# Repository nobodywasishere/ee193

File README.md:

# ee193

## Useful links

- https://www.seeedstudio.com/LoRa-E5-Dev-Kit-p-4868.html
- https://www.st.com/en/microcontrollers-microprocessors/stm32wle5jc.html#
- https://www.digikey.com/en/products/detail/seeed-technology-co-ltd/113990934/13926230

- https://docs.platformio.org/en/latest/boards/ststm32/nucleo_wl55jc.html
- https://github.com/platformio/platform-ststm32/blob/develop/boards/nucleo_wl55jc.json
- https://docs.zephyrproject.org/2.7.0/boards/arm/lora_e5_dev_board/doc/lora_e5_dev_board.html
- https://doc.riot-os.org/group__boards__lora-e5-dev.html

- https://www.st.com/en/development-tools/stm32cubeprog.html

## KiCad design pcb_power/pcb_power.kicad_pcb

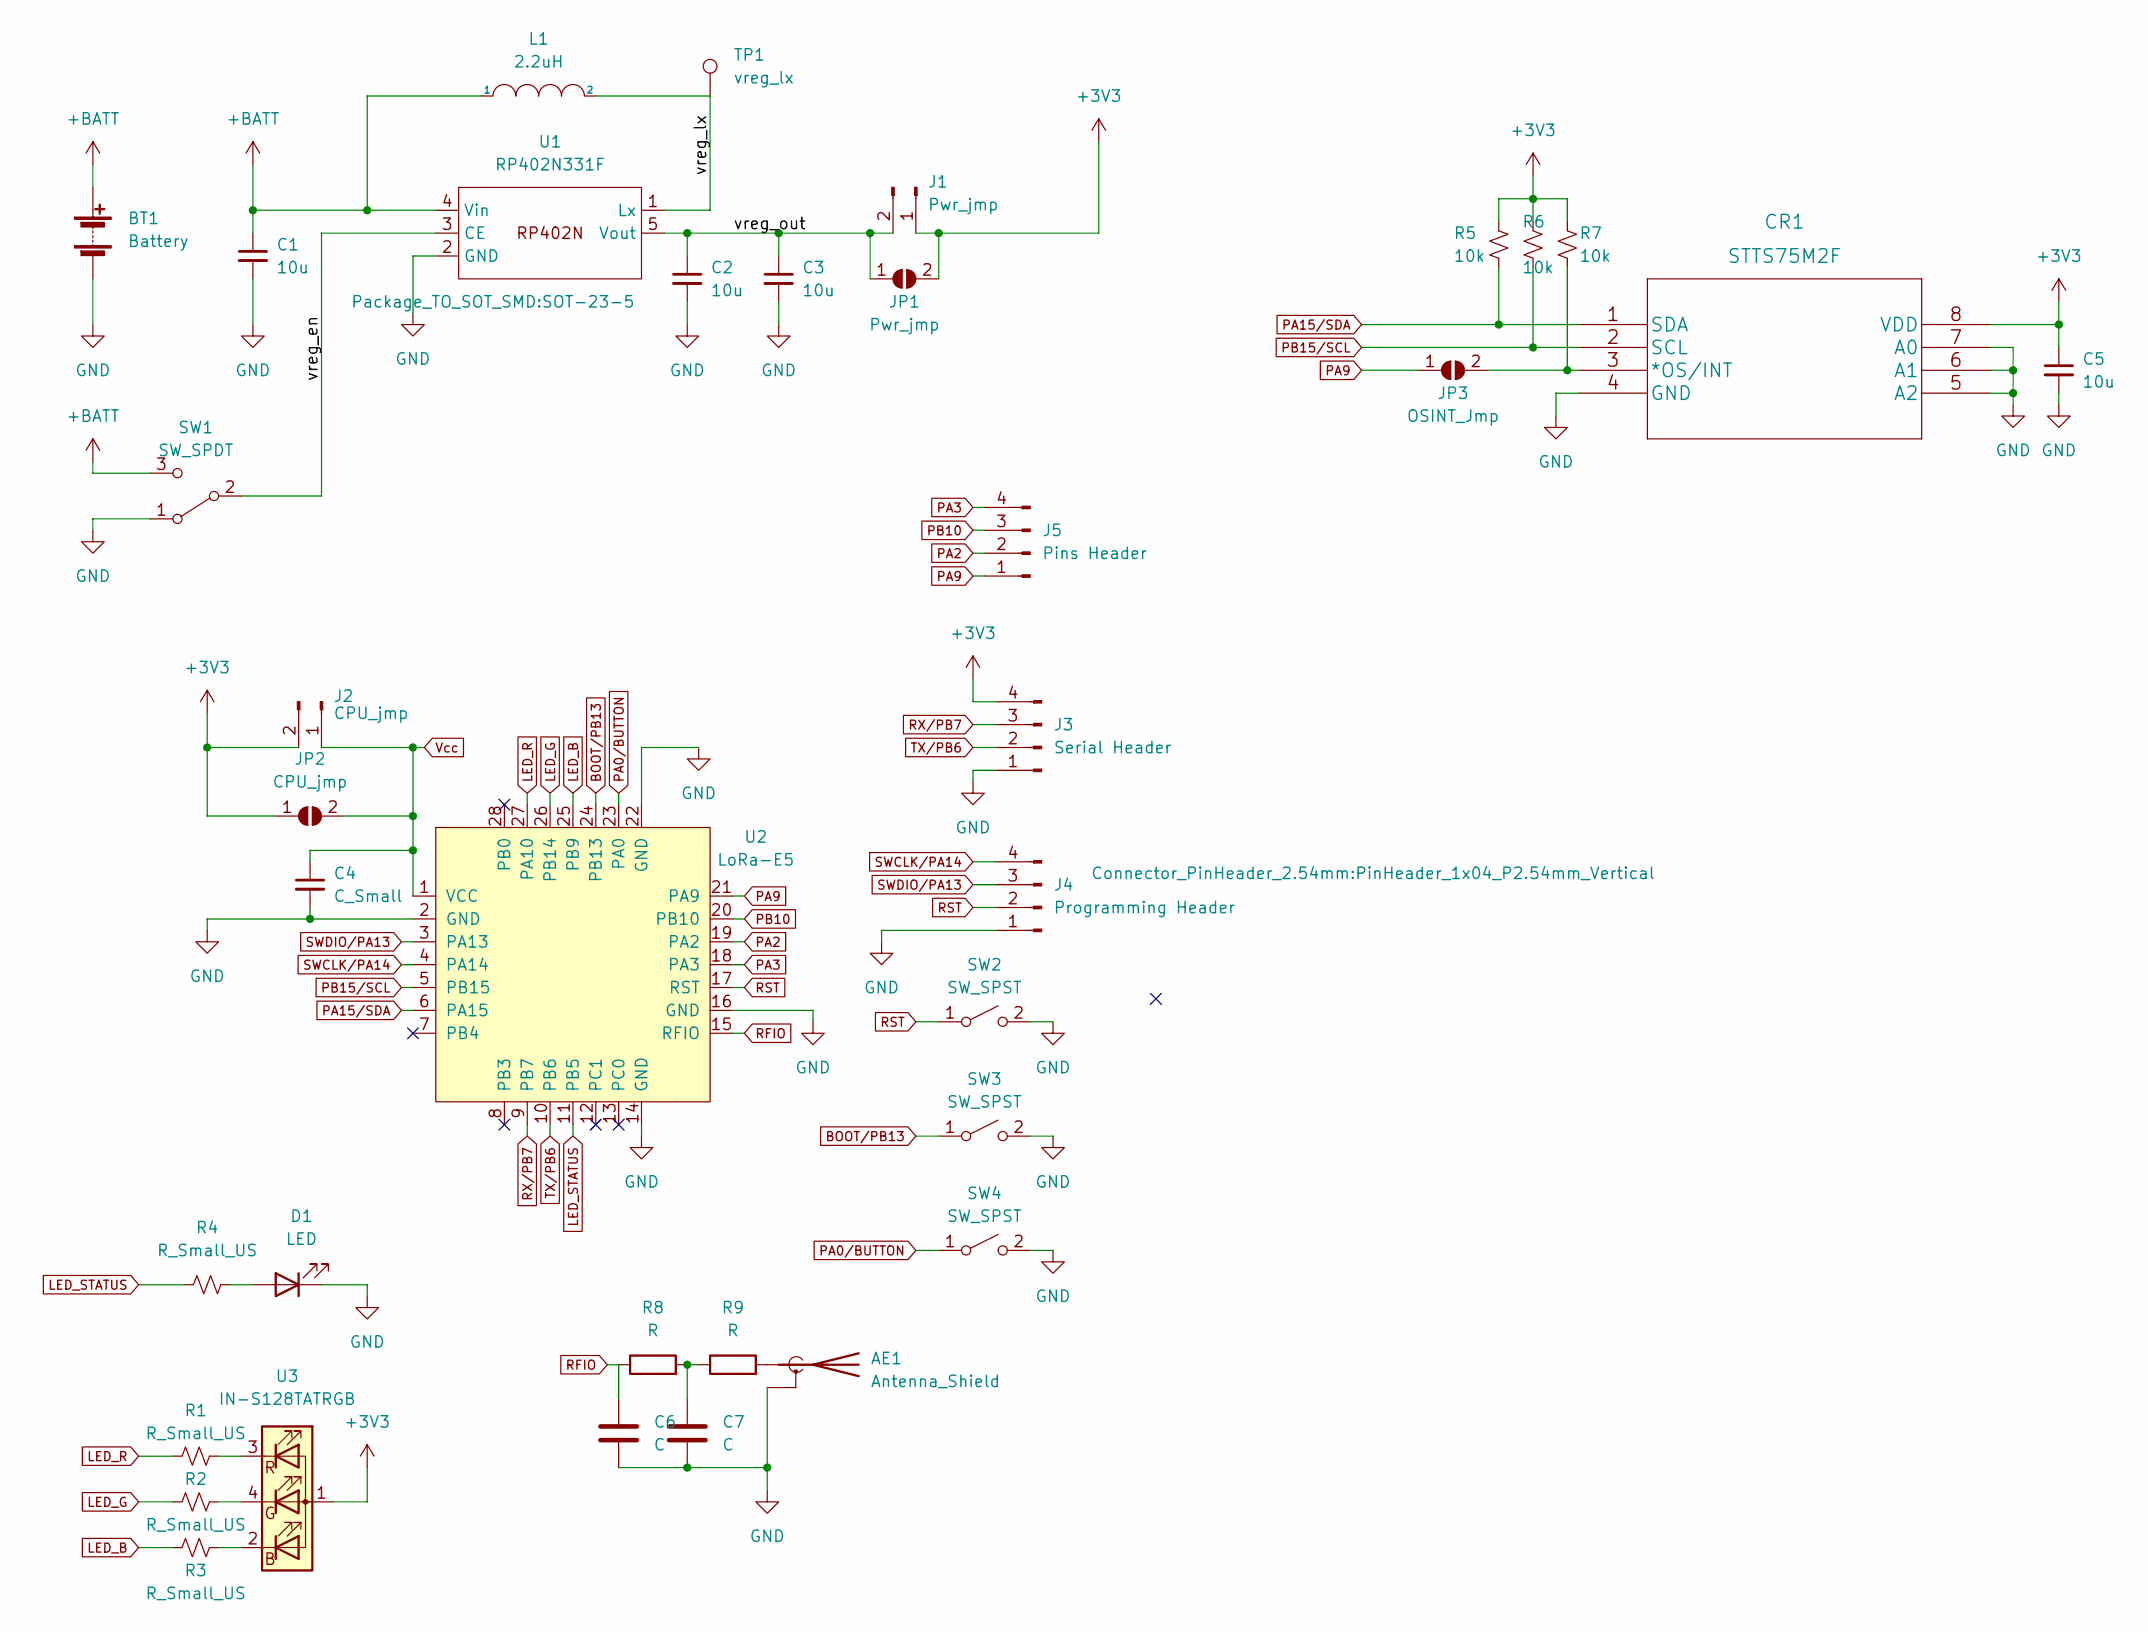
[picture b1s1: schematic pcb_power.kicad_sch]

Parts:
AE1: Antenna_Shield; U.FL_Molex_MCRF_73412-0110_Vertical
BT1: Battery; PinHeader_1x02_P2.54mm_Horizontal
C1, C2, C3, C5: 10u; C_0805_2012Metric
C4: C_Small; C_0805_2012Metric
C6, C7: C; C_0603_1608Metric_Pad1.08x0.95mm_HandSolder
CR1: STTS75M2F
D1: LED; LED_0805_2012Metric
J1: Pwr_jmp; PinHeader_1x02_P2.54mm_Vertical
J2: CPU_jmp; PinHeader_1x02_P2.54mm_Vertical
J3: Serial Header; PinHeader_1x04_P2.54mm_Vertical
J4: Programming Header; PinHeader_1x04_P2.54mm_Vertical
J5: Pins Header; PinHeader_1x04_P2.54mm_Vertical_SMD_Pin1Left
JP1: Pwr_jmp; SolderJumper-2_P1.3mm_Open_TrianglePad1.0x1.5mm
JP2: CPU_jmp; SolderJumper-2_P1.3mm_Open_TrianglePad1.0x1.5mm
JP3: OSINT_Jmp; SolderJumper-2_P1.3mm_Bridged2Bar_Pad1.0x1.5mm
L1: 2.2uH; TDK-VLS3012HBX-0-0-MFG
R1, R2, R3, R4: R_Small_US; R_0805_2012Metric
R5, R6, R7: 10k; R_0805_2012Metric
R8, R9: R; R_0603_1608Metric_Pad0.98x0.95mm_HandSolder
SW1: SW_SPDT; SW_SPDT_CK-JS102011SAQN
SW2, SW3, SW4: SW_SPST; SW_SPST_CK_RS282G05A3
TP1: vreg_lx; TestPoint_Pad_2.0x2.0mm
U1: RP402N331F; SOT-23-5
U2: LoRa-E5
U3: IN-S128TATRGB

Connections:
+3V3: C5.1, CR1.8 (VDD), J1.1, J2.2, J3.4, JP1.2 (B), JP2.1 (A), R5.1, R6.1, R7.1, U3.1 (A)
+BATT: BT1.1 (+), C1.1, L1.1, SW1.3 (C), U1.4 (Vin); also elsewhere on the board
/vreg_en: SW1.2 (B), U1.3 (CE); also elsewhere on the board
/vreg_lx: L1.2, TP1.1, U1.1 (Lx)
/vreg_out: C2.1, C3.1, J1.2, JP1.1 (A), U1.5 (Vout); also elsewhere on the board
BOOT/PB13: SW3.1 (A), U2.24 (PB13~)
GND: AE1.2 (Shield), BT1.2 (-), C1.2, C2.2, C3.2, C4.2, C5.2, C6.2, C7.2, CR1.4 (GND), CR1.5 (A2), CR1.6 (A1), CR1.7 (A0), D1.1 (K), J3.1, J4.1, SW1.1 (A), SW2.2 (B), SW3.2 (B), SW4.2 (B), U1.2 (GND), U2.2 (GND), U2.14 (GND), U2.16 (GND), U2.22 (GND); also elsewhere on the board
LED_B: R3.1, U2.25 (PB9)
LED_G: R2.1, U2.26 (PB14)
LED_R: R1.1, U2.27 (PA10)
LED_STATUS: R4.1, U2.11 (PB5)
unnamed: AE1.1 (A), R9.2
unnamed: C7.1, R8.2, R9.1
unnamed: CR1.3 (*OS/INT), JP3.2 (B), R7.2
unnamed: D1.2 (A), R4.2
unnamed: R1.2, U3.3 (RK)
unnamed: R2.2, U3.4 (GK)
unnamed: R3.2, U3.2 (BK)
PA0/BUTTON: SW4.1 (A), U2.23 (PA0)
PA2: J5.2, U2.19 (PA2)
PA3: J5.4, U2.18 (PA3)
PA9: J5.1, JP3.1 (A), U2.21 (PA9)
PA15/SDA: CR1.1 (SDA), R5.2, U2.6 (PA15)
PB10: J5.3, U2.20 (PB10)
PB15/SCL: CR1.2 (SCL), R6.2, U2.5 (PB15)
RFIO: C6.1, R8.1, U2.15 (RFIO)
RST: J4.2, SW2.1 (A), U2.17 (RST)
RX/PB7: J3.3, U2.9 (PB7)
SWCLK/PA14: J4.4, U2.4 (PA14)
SWDIO/PA13: J4.3, U2.3 (PA13)
TX/PB6: J3.2, U2.10 (PB6)
Vcc: C4.1, J2.1, JP2.2 (B), U2.1 (VCC)

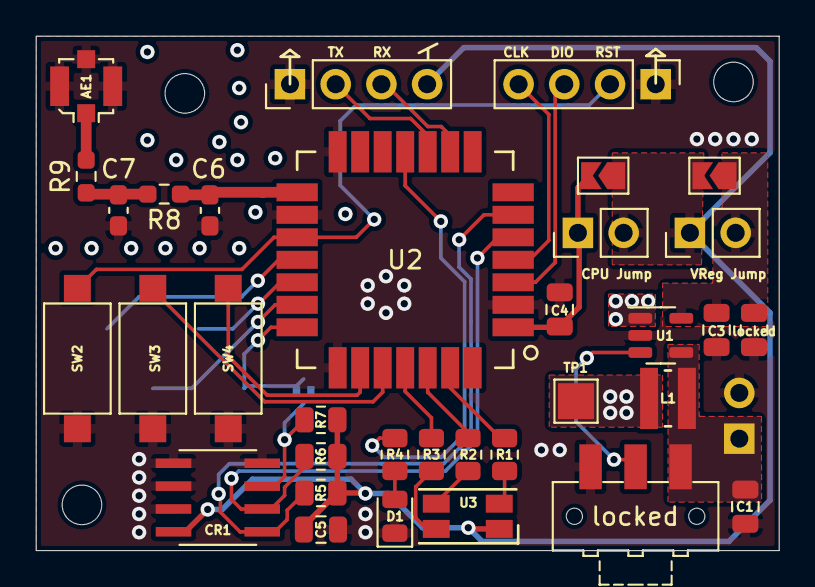
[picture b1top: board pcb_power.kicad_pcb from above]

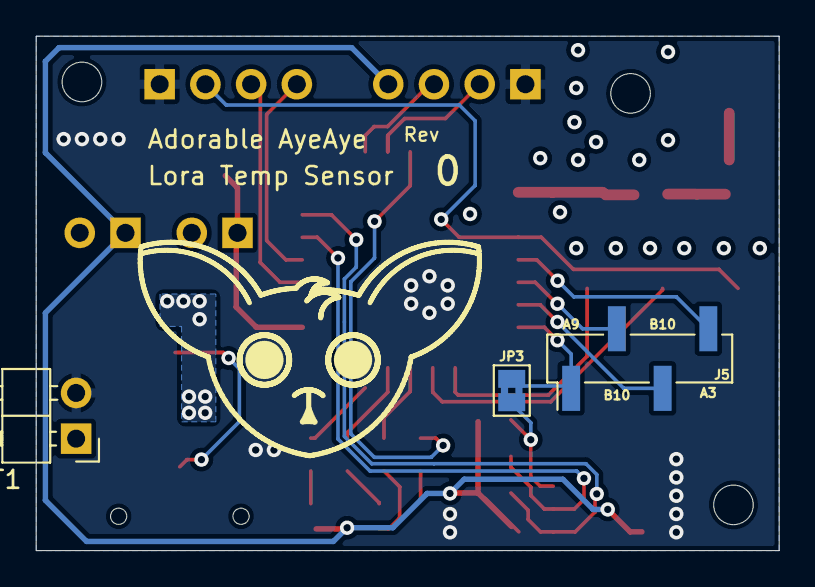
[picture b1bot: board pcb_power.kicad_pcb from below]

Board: 2 copper layers, 41.3 x 28.6 mm, 37 parts (3 on the bottom side), 32 nets.

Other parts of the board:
locked: locked; SW_SPDT_CK-JS102011SAQN
locked#2: locked; C_0805_2012Metric

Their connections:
+BATT: locked.3 (C); also elsewhere on the board
/vreg_en: locked.2 (B); also elsewhere on the board
/vreg_out: locked#2.1; also elsewhere on the board
GND: locked.1 (A), locked#2.2; also elsewhere on the board

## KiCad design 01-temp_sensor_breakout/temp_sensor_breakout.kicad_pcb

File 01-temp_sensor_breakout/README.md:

# Temperature Sensor Breakout Board

This is a breakout board for the [ST STTS75M2F](https://octopart.com/stts75m2f-stmicroelectronics-7124544) and [TDK NTCG103JF103FT1](https://octopart.com/ntcg103jf103ft1-tdk-19035495) design with KiCAD 6. PCB image generated using [PcbDraw](https://github.com/yaqwsx/PcbDraw).

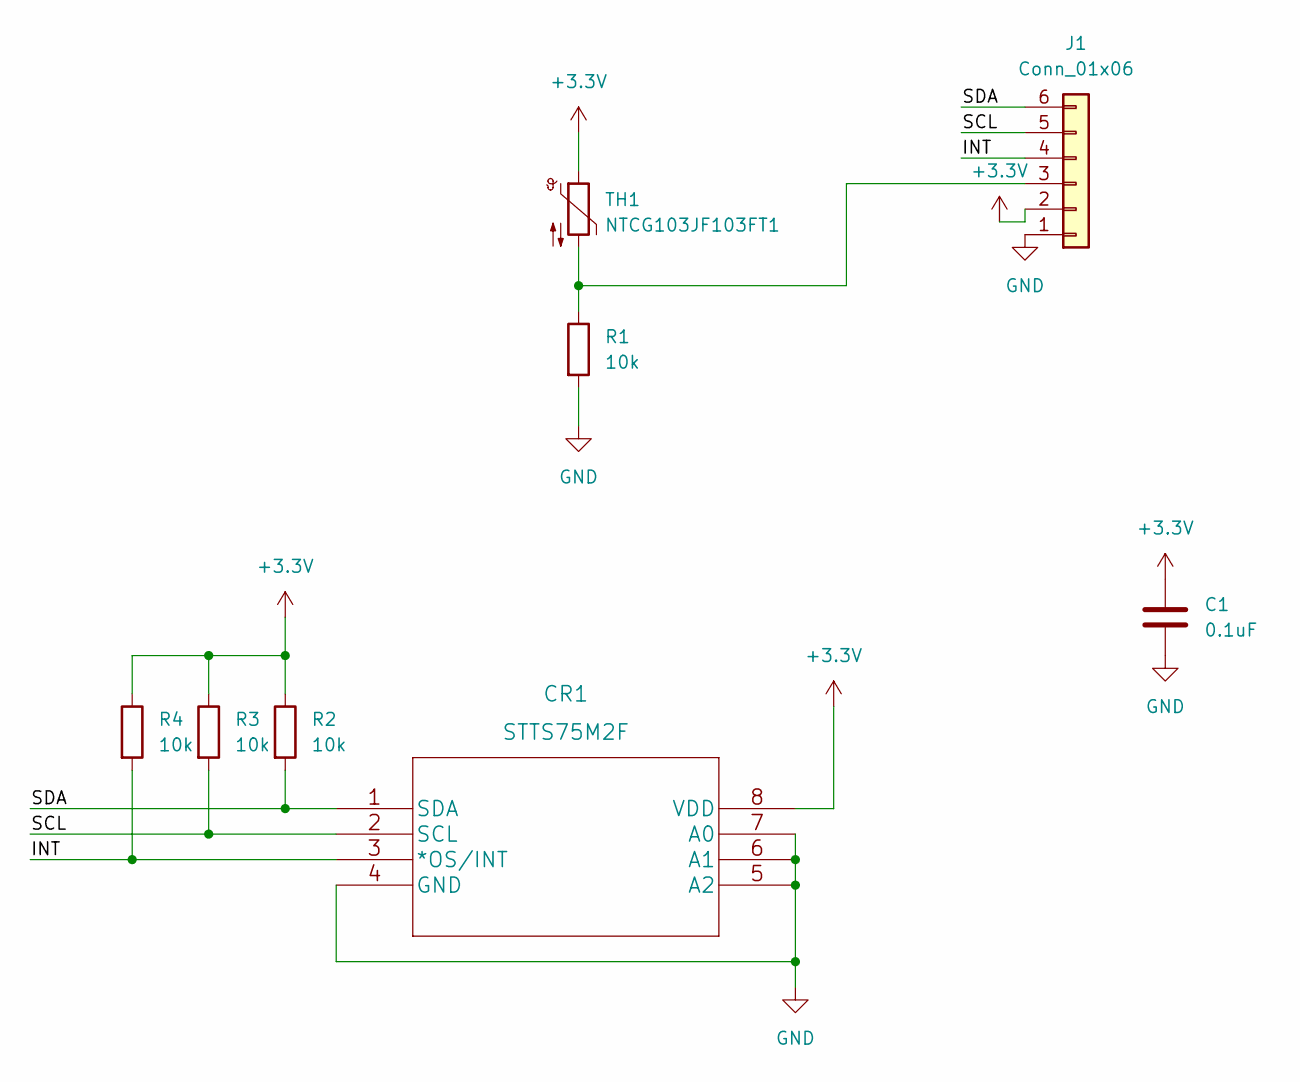
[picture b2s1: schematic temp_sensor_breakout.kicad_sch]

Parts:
C1: 0.1uF; C_0603_1608Metric
CR1: STTS75M2F
J1: Conn_01x06; PinHeader_1x06_P2.54mm_Vertical
R1, R2, R3, R4: 10k; R_0603_1608Metric
TH1: NTCG103JF103FT1; R_0402_1005Metric

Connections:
+3V3: C1.1, CR1.8 (VDD), J1.2, R2.1, R3.1, R4.1, TH1.1
/INT: CR1.3 (*OS/INT), J1.4, R4.2
/SCL: CR1.2 (SCL), J1.5, R3.2
/SDA: CR1.1 (SDA), J1.6, R2.2
GND: C1.2, CR1.4 (GND), CR1.5 (A2), CR1.6 (A1), CR1.7 (A0), J1.1, R1.2
unnamed: J1.3, R1.1, TH1.2

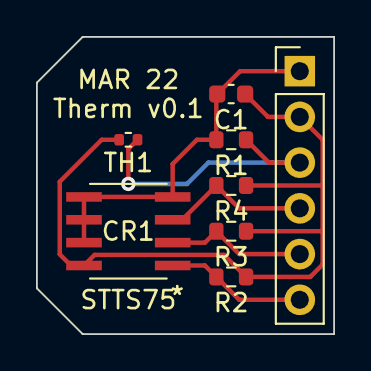
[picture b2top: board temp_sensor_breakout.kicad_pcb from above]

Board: 2 copper layers, 16.5 x 16.5 mm, 8 parts (0 on the bottom side), 6 nets.

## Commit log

2022-02-08 Add datasheet and useful links
2022-02-09 More documentation
2022-02-09 Start of a basic example
2022-02-11 Add temp_sensor_breakout files
2022-02-11 Get CMSIS working
2022-02-11 Rename blinky project folder
2022-02-11 Seperate blinky by supported framework
2022-02-15 Remove baremetal example due to not passing verification on upload
2022-02-15 Correctly working blink for stm32cube and cmsis frameworks
2022-02-19 Add zephyr blinky example
2022-02-19 zephyr-adc starter code
2022-02-23 Somewhat working ADC example?
2022-03-08 Working ADC
2022-03-11 adc test successful
2022-04-06 power management stuff
2022-04-08 added power stuff to pcb
2022-04-09 more work on pwr circuitry schematic
2022-04-10 Power Layout
2022-04-11 More PCB Work
2022-04-14 Lili rework 2
2022-04-14 DRC Fixes, etc
2022-04-14 Final ZP changes before antenna rework and cosmetix
2022-04-14 sensor measurements
2022-04-25 Lora send/recv working
2022-04-25 Test of i2c
2022-04-25 Add .gitignore and remove DS_Store
2022-05-04 Arduino i2c finder
2022-05-04 Working I2C w/ temp sensor reading
2022-05-04 Initial version of final working code
2022-05-05 Refined wifi transmit, add led colors, header copyright notice
2022-05-05 Add headers to all files
2022-05-05 Basic uart -> mqtt bridge
2022-05-06 Power experiments Co-authored-by: zpogrebin <zpogrebin@users.noreply.github.com>
2022-05-06 Fixing I2C to be more robust Co-authored-by: zpogrebin <zpogrebin@users.noreply.github.com>
2022-05-06 Send node id's for node code, add server code, update pybridge

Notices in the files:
parts and their libraries:
Copyright 2021 Accelerated Designs. All rights reserved.
